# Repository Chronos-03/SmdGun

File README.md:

# Chronos-858D: Custom ESP32-S3 Hot Air Rework Station

## 1. Project Overview
The **Chronos-858D** is a custom-engineered, smart benchtop hot air rework station built around the **ESP32-S3-DevKitC-1** that combines microcontroller precision with robust AC/DC power electronics. Designed from the ground up with a custom 2-layer KiCad PCB and a 3D-printed Fusion 360 enclosure, the station regulates a 220V AC 700W ceramic heating element using  PID control through a  optical isolation stage while independently driving a 24V DC brushless blower fan via PWM. For workshop safety  a physical roller-lever microswitch mounted on the handle cradle automatically detects when the hot air gun is docked, immediately cutting power to the heater coil and running a timed 1-minute cooling cycle until the nozzle drops safely below 50°C, with all real-time temperature measuring, airflow power, and with the stats on a 2.8-inch ILI9341 SPI TFT display controlled by 2 rotary encoders.

---

## 2. Final CAD Renders & Enclosure Design
The enclosure and external handle holder are fully modeled in Fusion 360  for 3D printing in heat-resistant PETG or ABS, and also have an angled front instrument panel and ventilated case that house both the custom main PCB and the 24V 3A industrial SMPS in a compact case. To add tight 3mm thread depths and 3.2mm mounting holes on the display and main circuit board, the internal standoffs are designed around M3 × 3mm knurled brass heat-set inserts paired with M3 × 4mm pan head machine screws, while the side-mounted integrates a recessed slot for a KW11-3Z roller limit switch positioned along the cool lower grip of the 858D handle so the resting weight of the wand actuates the cooldown switch smoothly without exposing the switch body to nozzle heat.

---

## 3. ⚠️ High-Voltage Safety Warning
> **DANGER — 220V–240V AC MAINS VOLTAGE:** This rework station interfaces directly with lethal 220V–240V AC mains electricity to power the 700W heating element and internal SMPS, which presents a severe risk of electrocution, burns, or fire if handled improperly. Always disconnect the main AC power cord from the wall outlet before opening the enclosure, probing the circuit board, or modifying any wiring, and strictly maintain the 2.5mm physical creepage and clearance gap on the PCB between the high-voltage AC heater section and the low-voltage DC microcontroller logic. Ensure that the incoming protective earth ground pin on the IEC320 C14 socket is securely bonded to the metal frame of the 24V SMPS and the insulated-tab BTA16-600B TRIAC heatsink, and insulate all high-voltage solder joints and terminal connections using polyolefin heat shrink tubing and high-temperature polyimide Kapton tape before powering the system.

---

## 4. Electronic Specifications & Pinout
The electrical designing  separates high-voltage AC switching from low-voltage 3.3V digital control across a custom 2-layer  PCB powered by a 24V DC 3A (72W) enclosed SMPS protected by a 2A resettable PTC polyfuse . An onboard LM2596 buck converter  steps the 24V rail down to a regulated 5.0V DC to feed the ESP32-S3-DevKitC-1 , while the 24V blower fan is controllerd through an IRLZ44N logic-level N-channel MOSFET , paired with a 10kΩ gate pull-down resistor , 220Ω gate resistor , and 1N4007 flyback clamping diode . 

On the isolated AC side  protected by a 5A 250V fast-blow glass fuse , HEATER_PWM  drives an MOC3041 zero-crossing optocoupler  through a 150Ω current-limiting resistor , which triggers a 16A 600V BTA16-600B TRIAC  via a 360Ω 1W gate resistor  and a 39Ω 2W / 0.01µF 275VAC X2 RC snubber network . Closed-loop temperature feedback from the handle's K-type thermocouple  is digitized by a MAX6675 cold-junction compensated amplifier  sharing the hardware SPI bus with the non-touch 9-pin 2.8" ILI9341 240×320 TFT display (`J3`), alongside two EC11 rotary encoders  and the holder  limit switch.

## 5. Enclosure & Case Assembly
pressing the M3 × 3mm brass heat-set inserts flush into the 3D-printed mounting bosses inside the front bezel and main chassis floor, then pre-tune the LM2596 buck converter  with a multimeter to output exactly 5.0V DC before seating the ESP32-S3 into its female headers. Next, mount the 2.8-inch ILI9341 TFT display and the populated main PCB onto the internal standoffs using M3 × 4mm pan head screws, fasten the two EC11 rotary encoders and the GX16-8 aviation panel socket to the front face, and bolt the TO-220 aluminum heatsink onto the BTA16-600B TRIAC  with a thin layer of thermal paste. Secure the 24V 3A SMPS to the base of the enclosure double-sided heavy-duty foam tape, snap the IEC320 C14 AC mains inlet switch into the rear panel cutout, and fasten the KW11-3Z roller limit switch onto the external handle cradle using M2 screws and nuts. Finally, wire the 16 AWG silicone power cables from the IEC inlet and SMPS to the screw terminal blocks  and the 24 AWG signal wires from the cradle switch , insulating all exposed AC and DC joints with heat shrink tubing and Kapton tape before closing the case and verifying electrical isolation with a continuity test.

---

## 6. Firmware Architecture & Cooldown Logic
The ESP32-S3 firmware runs a non-blocking C++ control loop that continuously polls the MAX6675 sensor over hardware SPI every 250ms, feeds the nozzle temperature into a PID control algorithm to update the zero-crossing heater duty cycle on `GPIO 4` (`HEATER_PWM`), and refreshes the 2.8-inch ILI9341 TFT display while tracking rotary encoder interrupts for instant target temperature and fan speed adjustments. When the user places the hot air gun into the cradle, the weight of the handle depresses the KW11-3Z roller lever and pulls `GPIO 6` (`REED_SW`) to `GND` (`LOW`), which immediately forces the heater output to `0%`, switches the UI to Cooldown Mode, and locks the 24V blower fan (`GPIO 5`) at 80%–100% speed for a full 1-minute cooldown timer (and until the thermocouple reading drops below 50°C) before shutting the fan off completely and entering low-power

### **Chronos-858D Master Bill of Materials (BOM)**

| # | Component | Supplier | Qty | Total (INR) | Total (USD) | Product Link |
| :--- | :--- | :--- | :---: | :---: | :---: | :--- |
| **1** | Custom 3D-Printed Enclosure + Cradle | PrintLegion | 1 | ₹2,500 | $26.88 | [Link](https://printinglegion.hackclub.com) |
| **2** | Custom 2-Layer PCB Manufacturing | Robu | 1 | ₹900 | $9.68 | [Link](https://robu.in/) |
| **3** | ESP32-S3-DevKitC-1-N8R8 | Robu | 1 | ₹1,839 | $19.77 | [Link](https://robu.in/product/espressif-esp32-s3-devkitc-1-n8r8-development-board/) |
| **4** | 2.4" SPI TFT Touch Screen Module | MakerBazar | 1 | ₹679 | $7.30 | [Link](https://makerbazar.in/products/2-4-inch-spi-interface-240-320-tft-display-module?variant=44937178022128) |
| **5** | MAX6675 Thermocouple Module | MakerBazar | 1 | ₹309 | $3.32 | [Link](https://makerbazar.in/products/max6675-thermocouple-sensor-module) |
| **6** | LM2596 DC-DC Buck Step-Down Module | MakerBazar | 1 | ₹79 | $0.85 | [Link](https://makerbazar.in/products/lm2596-dc-dc-converter-step-down-module?variant=48251191918832) |
| **7** | Quick 858D Replacement Handle (8-wire) | TonyVision | 1 | ₹649 | $6.98 | [Link](https://www.tonyvision.in/product/30533442/Quick-858-Handle-For-858-SMD-Rework-Station--8-Wire-) |
| **8** | GX16-8 Aviation Socket (Panel Mount) | Probots | 1 | ₹160 | $1.72 | [Link](https://probots.co.in/8-pin-gx16-male-to-female-aviation-plug.html) |
| **9** | 24V 3A Metal Enclosed SMPS | ElecComp | 1 | ₹500 | $5.38 | [Link](https://www.electronicscomp.com/24v-3amp-smps-dc-metal-power-supply-nwp-india) |
| **10** | KW11-3Z Roller Lever Micro Switch | MakerBazar | 1 | ₹20 | $0.22 | [Link](https://makerbazar.in/products/automation-direct-limit-switch?variant=46931163742448) |
| **11** | IEC320 C14 AC Mains Socket + Rocker | Probots | 1 | ₹210 | $2.26 | [Link](https://probots.co.in/3-pin-iec320-c14-ac-power-socket-with-fuse-red-rocker-switch-panel-mount-connector.html) |
| **12** | Finned Aluminum Heatsink Kit | MakerBazar | 3 | ₹87 | $0.94 | [Link](https://makerbazar.in/products/3pcs-aluminum-heatsink-with-thermal-tape-for-raspberry-pi-4-model-b-black?variant=48460430213360) |
| **13** | KF301 2-Pin 5.08mm Screw Terminal | Robu | 2 | ₹20 | $0.22 | [Link](https://robu.in/product/kf301-2-pin-5-08mm-pitch-plug-in-screw-terminal-block-connector-pack-of-5/) |
| **14** | 240V AC Power Cord 3-Pin to IEC C-13 | MakerBazar | 1 | ₹159 | $1.71 | [Link](https://makerbazar.in/products/240v-ac-power-cord-3-pin-to-iec-c-13-female-cable?variant=44609024262384) |
| **15** | 20AWG Flexible Silicone Wire (Green) | Robu | 1 | ₹50 | $0.54 | [Link](https://robu.in/product/high-quality-ultra-flexible-20awg-silicone-wire-1000m-green/) |
| **16** | BTA16-600B TRIAC (Pack of 5) | Amazon | 1 | ₹169 | $1.82 | [Link](https://www.amazon.in/pics-BTA16-600B-TRIAC-Volts/dp/B0C9VVTZTV/) |
| **17** | MOC3041M Zero-Cross Optoisolator | Robu | 1 | ₹50 | $0.54 | [Link](https://robu.in/product/moc3041m-ic-zero-cross-optoisolator-triac-driver-ic/) |
| **18** | IRLZ44N Logic-Level N-Channel MOSFET | Robu | 1 | ₹44 | $0.47 | [Link](https://robu.in/product/irlz44n/) |
| **19** | 1N4007 1W Rectifier Diode | Robu | 5 | ₹15 | $0.16 | [Link](https://robu.in/product/1n4007-1w-diode-pack-of-30/) |
| **20** | Hongyan EC11 Rotary Encoders | Robu | 2 | ₹116 | $1.25 | [Link](https://robu.in/product/hongyan-ec11h-7ce20p1zy20-rotary-encoder-with-push-button-switch-vertical-plug-in-5-pin/) |
| **21** | Loose M3 Screws, Nuts & 1m Heat Shrink | Local | 1 | ₹50 | $0.54 | *Local Hardware Store* |
| **22** | 330Ω 1/4W 1206 SMD Resistor | Robu | 1 | ₹15 | $0.16 | [Link](https://robu.in/product/330-ohm-1-4w-1206-surface-mount-chip-resistor-pack-of-100/) |
| **23** | 360Ω 0805 SMD Resistor (Yageo) | Robu | 1 | ₹15 | $0.16 | [Link](https://robu.in/product/rc0805fr-07360rl-yageo-360-ohms-%c2%b11-0-125w-1-8w-chip-resistor-0805-2012-metric-moisture-resistant-thick-film/) |
| **24** | 100Ω 1/4W 1206 SMD Resistor | Robu | 1 | ₹15 | $0.16 | [Link](https://robu.in/product/100-ohm-chip-resistor-1-4w-1206-surface-mount-pack-of-100/) |
| **25** | 10kΩ 0805 SMD Resistor | Amazon | 1 | ₹99 | $1.06 | [Link](https://www.amazon.in/Electronic-Spices-Power-Thick-Resistor/dp/B0BFD96R76/) |
| **26** | 100Ω 2W Carbon Film Resistor | Robu | 1 | ₹2.45 | $0.03 | [Link](https://robu.in/product/100-ohms-2w-carbon-film-resistor-pack-of-50/) |
| **27** | 100nF 400V DIP Polyester Film Cap | Robu | 1 | ₹6.00 | $0.06 | [Link](https://robu.in/product/100nf-400v-dip-polyester-film-capacitor-pitch10mm/) |
| **28** | 100nF 0805 SMD Ceramic Capacitor | Robu | 3 | ₹2.37 | $0.03 | [Link](https://robu.in/product/100nf-0805-surface-mount-multilayer-ceramic-capacitor-pack-of-40/) |
| **29** | 100µF 35V SMD Tantalum Capacitor | Robu | 1 | ₹57.00 | $0.61 | [Link](https://robu.in/product/100uf-35v-10-d-case-chip-tantalum-capacitorsmd-avx/) |
| **30** | DHRUV-PRO 120x120x38mm 24V Cooling Fan | Amazon | 1 | ₹579.00 | $6.23 | [Link](https://www.amazon.in/DHRUV-PRO-120X120X38mm-Cooling-120x120x38-MM-2800-RPM/dp/B0BTMC17SK/) |
| | **FINAL GRAND TOTAL** | | | **₹9,395.82** | **$101.05** | |

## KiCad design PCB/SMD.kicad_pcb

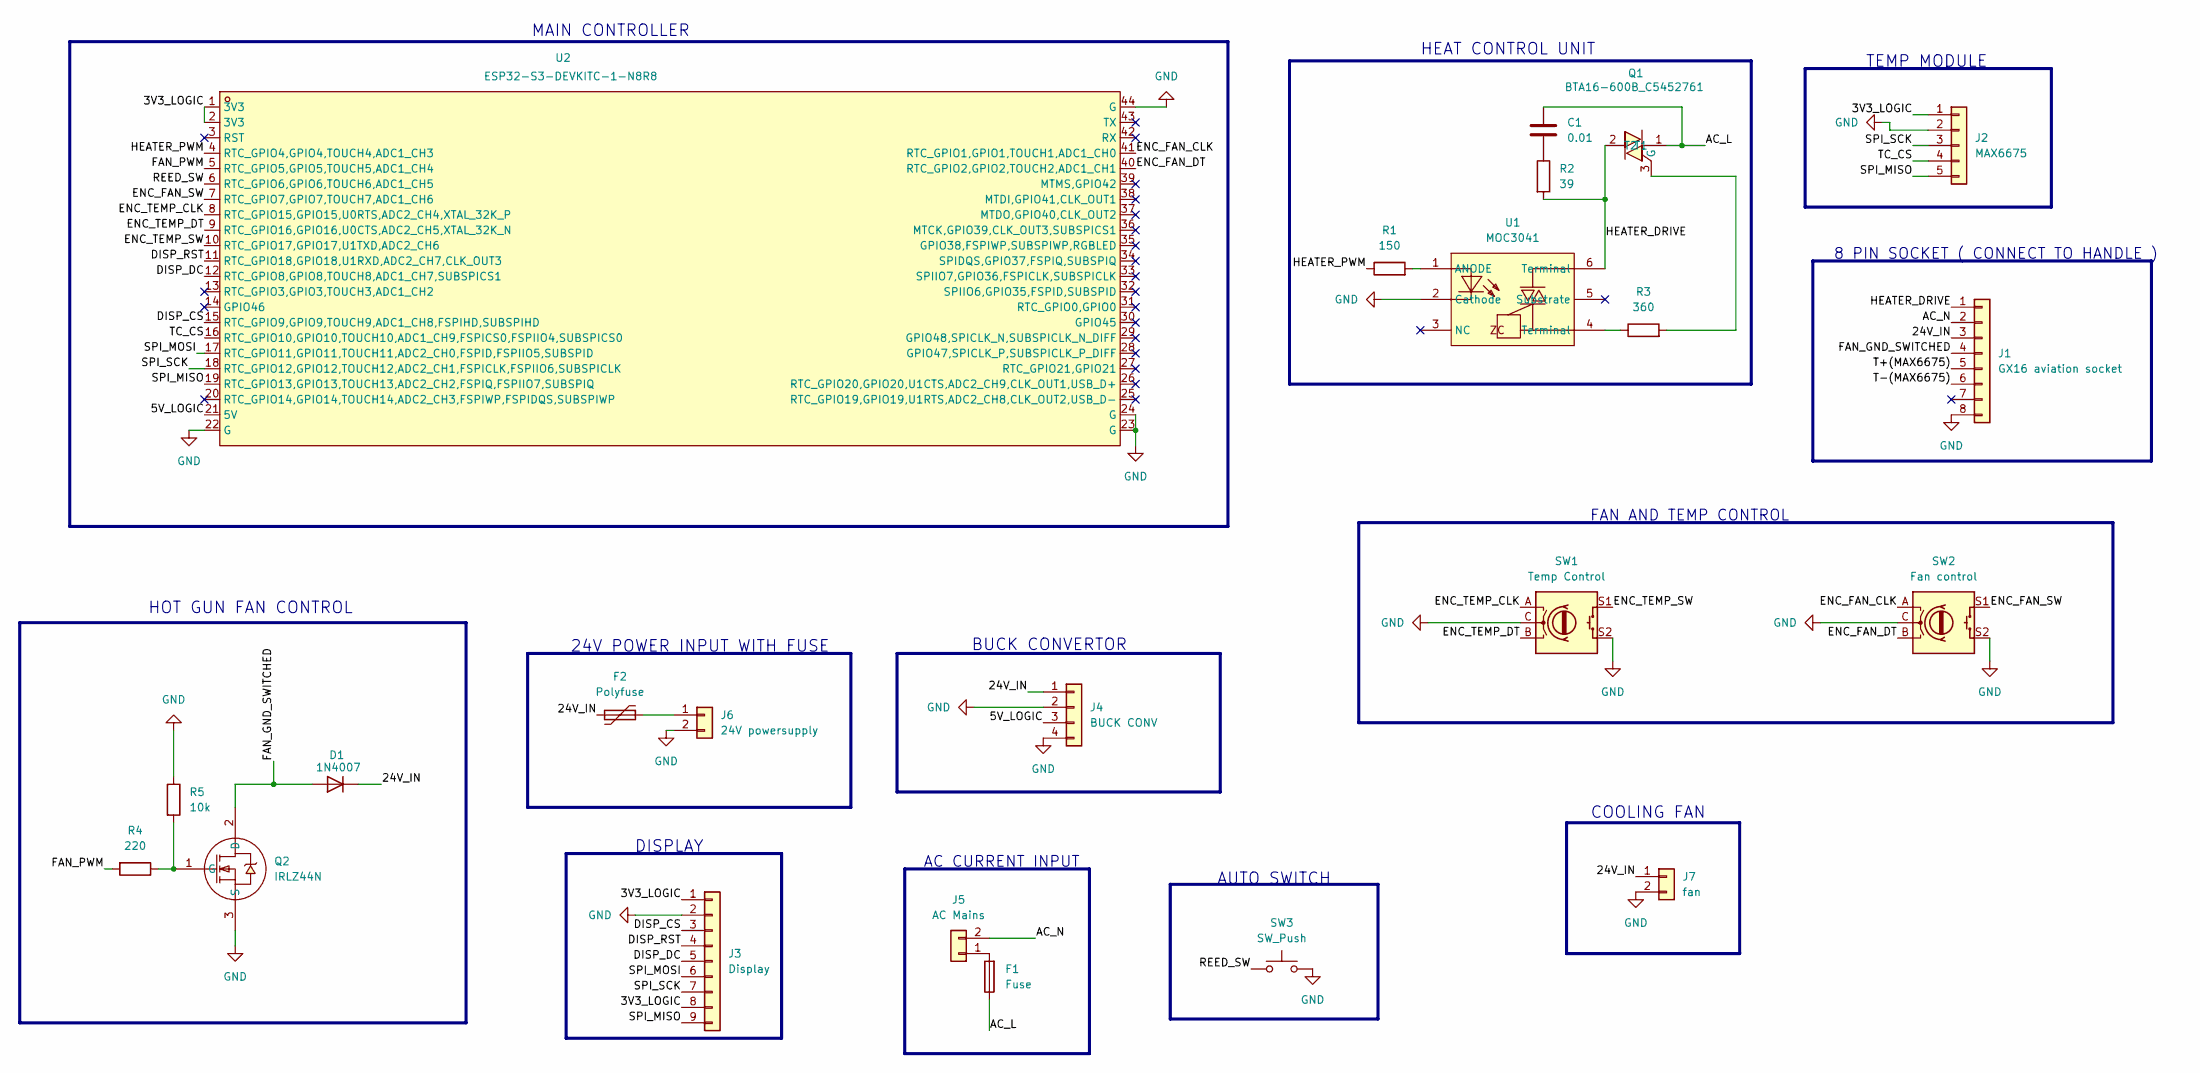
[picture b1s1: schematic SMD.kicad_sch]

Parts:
C1: 0.01; C_Rect_L18.0mm_W5.0mm_P15.00mm_FKS3_FKP3
D1: 1N4007; D_DO-41_SOD81_P10.16mm_Horizontal
F1: Fuse; Fuseholder_Cylinder-5x20mm_Schurter_0031_8201_Horizontal_Op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
F2: Polyfuse; Fuse_Bourns_MF-RHT200
J1: GX16 aviation socket; PinHeader_1x08_P2.54mm_Horizontal
J2: MAX6675; PinHeader_1x05_P2.54mm_Horizontal
J3: Display; PinHeader_1x09_P2.54mm_Horizontal
J4: BUCK CONV; PinHeader_1x04_P2.54mm_Horizontal
J5: AC Mains; TerminalBlock_Phoenix_MKDS-1,5-2-5.08_1x02_P5.08mm_Horizont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
J6: 24V powersupply; TerminalBlock_Phoenix_MKDS-1,5-2-5.08_1x02_P5.08mm_Horizont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
J7: fan; PinHeader_1x02_P2.54mm_Vertical
Q1: BTA16-600B_C5452761; TO-220-3_L10.0-W4.5-P2.54-L_1; MPN BTA16-600B; LCSC Part C5452761
Q2: IRLZ44N; TO-220-3_L10.2-W4.5-P2.54-L; MPN IRLZ44N(UMW); LCSC Part C42370423
R1: 150; R_0805_2012Metric
R2: 39; R_Axial_DIN0414_L11.9mm_D4.5mm_P15.24mm_Horizontal
R3: 360; R_0805_2012Metric
R4: 220; R_0805_2012Metric
R5: 10k; R_0805_2012Metric
SW1: Temp Control; RotaryEncoder_Alps_EC11E-Switch_Vertical_H20mm
SW2: Fan control; RotaryEncoder_Alps_EC11E-Switch_Vertical_H20mm
SW3: SW_Push; PinHeader_1x02_P2.54mm_Vertical
U1: MOC3041; DIP-6_L7.3-W6.5-P2.54-LS7.6-BL; MPN MOC3041; LCSC Part C6177963
U2: ESP32-S3-DEVKITC-1-N8R8; CONN-TH_ESP32-S3-DEVKITC-1U-N8; MPN ESP32-S3-DEVKITC-1-N8R8; LCSC Part C20541519

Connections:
/3V3_LOGIC: J2.1, J3.1, J3.8, U2.1 (3V3), U2.2 (3V3)
/5V_LOGIC: J4.3, U2.21 (5V)
/24V_IN: D1.1 (K), F2.2, J1.3, J4.1, J7.1
/AC_L: C1.1, F1.1, Q1.1 (T1)
/AC_N: J1.2, J5.2
/DISP_CS: J3.3, U2.15 (RTC_GPIO9,GPIO9,TOUCH9,ADC1_CH8,FSPIHD,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)
/DISP_DC: J3.5, U2.12 (RTC_GPIO8,GPIO8,TOUCH8,ADC1_CH7,SUBSPIC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)
/DISP_RST: J3.4, U2.11 (RTC_GPIO18,GPIO18,U1RXD,ADC2_CH7,CLK_OU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)
/ENC_FAN_CLK: SW2.A, U2.41 (RTC_GPIO1,GPIO1,TOUCH1,ADC1_CH0)
/ENC_FAN_DT: SW2.B, U2.40 (RTC_GPIO2,GPIO2,TOUCH2,ADC1_CH1)
/ENC_FAN_SW: SW2.S1, U2.7 (RTC_GPIO7,GPIO7,TOUCH7,ADC1_CH6)
/ENC_TEMP_CLK: SW1.A, U2.8 (RTC_GPIO15,GPIO15,U0RTS,ADC2_CH4,XTAL_3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)
/ENC_TEMP_DT: SW1.B, U2.9 (RTC_GPIO16,GPIO16,U0CTS,ADC2_CH5,XTAL_3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)
/ENC_TEMP_SW: SW1.S1, U2.10 (RTC_GPIO17,GPIO17,U1TXD,ADC2_CH6)
/FAN_GND_SWITCHED: D1.2 (A), J1.4, Q2.2 (D)
/FAN_PWM: R4.2, U2.5 (RTC_GPIO5,GPIO5,TOUCH5,ADC1_CH4)
/HEATER_DRIVE: J1.1, Q1.2 (T2), R2.2, U1.6 (Terminal)
/HEATER_PWM: R1.1, U2.4 (RTC_GPIO4,GPIO4,TOUCH4,ADC1_CH3)
/REED_SW: SW3.1, U2.6 (RTC_GPIO6,GPIO6,TOUCH6,ADC1_CH5)
/SPI_MISO: J2.5, J3.9, U2.19 (RTC_GPIO13,GPIO13,TOUCH13,ADC2_CH2,FSPI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)
/SPI_MOSI: J3.6, U2.17 (RTC_GPIO11,GPIO11,TOUCH11,ADC2_CH0,FSPI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)
/SPI_SCK: J2.3, J3.7, U2.18 (RTC_GPIO12,GPIO12,TOUCH12,ADC2_CH1,FSPI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)
/T+(MAX6675): J1.5
/T-(MAX6675): J1.6
/TC_CS: J2.4, U2.16 (RTC_GPIO10,GPIO10,TOUCH10,ADC1_CH9,FSPI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)
GND: J1.8, J2.2, J3.2, J4.2, J4.4, J6.2, J7.2, Q2.3 (S), R5.1, SW1.C, SW1.S2, SW2.C, SW2.S2, SW3.2, U1.2 (Cathode), U2.22 (G), U2.23 (G), U2.24 (G), U2.44 (G)
unnamed: C1.2, R2.1
unnamed: F1.2, J5.1
unnamed: F2.1, J6.1
unnamed: Q1.3 (G), R3.2
unnamed: Q2.1 (G), R4.1, R5.2
unnamed: R3.1, U1.4 (Terminal)
unnamed: R1.2, U1.1 (ANODE)

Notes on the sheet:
HOT GUN FAN CONTROL
DISPLAY
MAIN CONTROLLER
AUTO SWITCH
BUCK CONVERTOR
AC CURRENT INPUT
TEMP MODULE
24V POWER INPUT WITH FUSE
8 PIN SOCKET ( CONNECT TO HANDLE )
FAN AND TEMP CONTROL
HEAT CONTROL UNIT
COOLING FAN

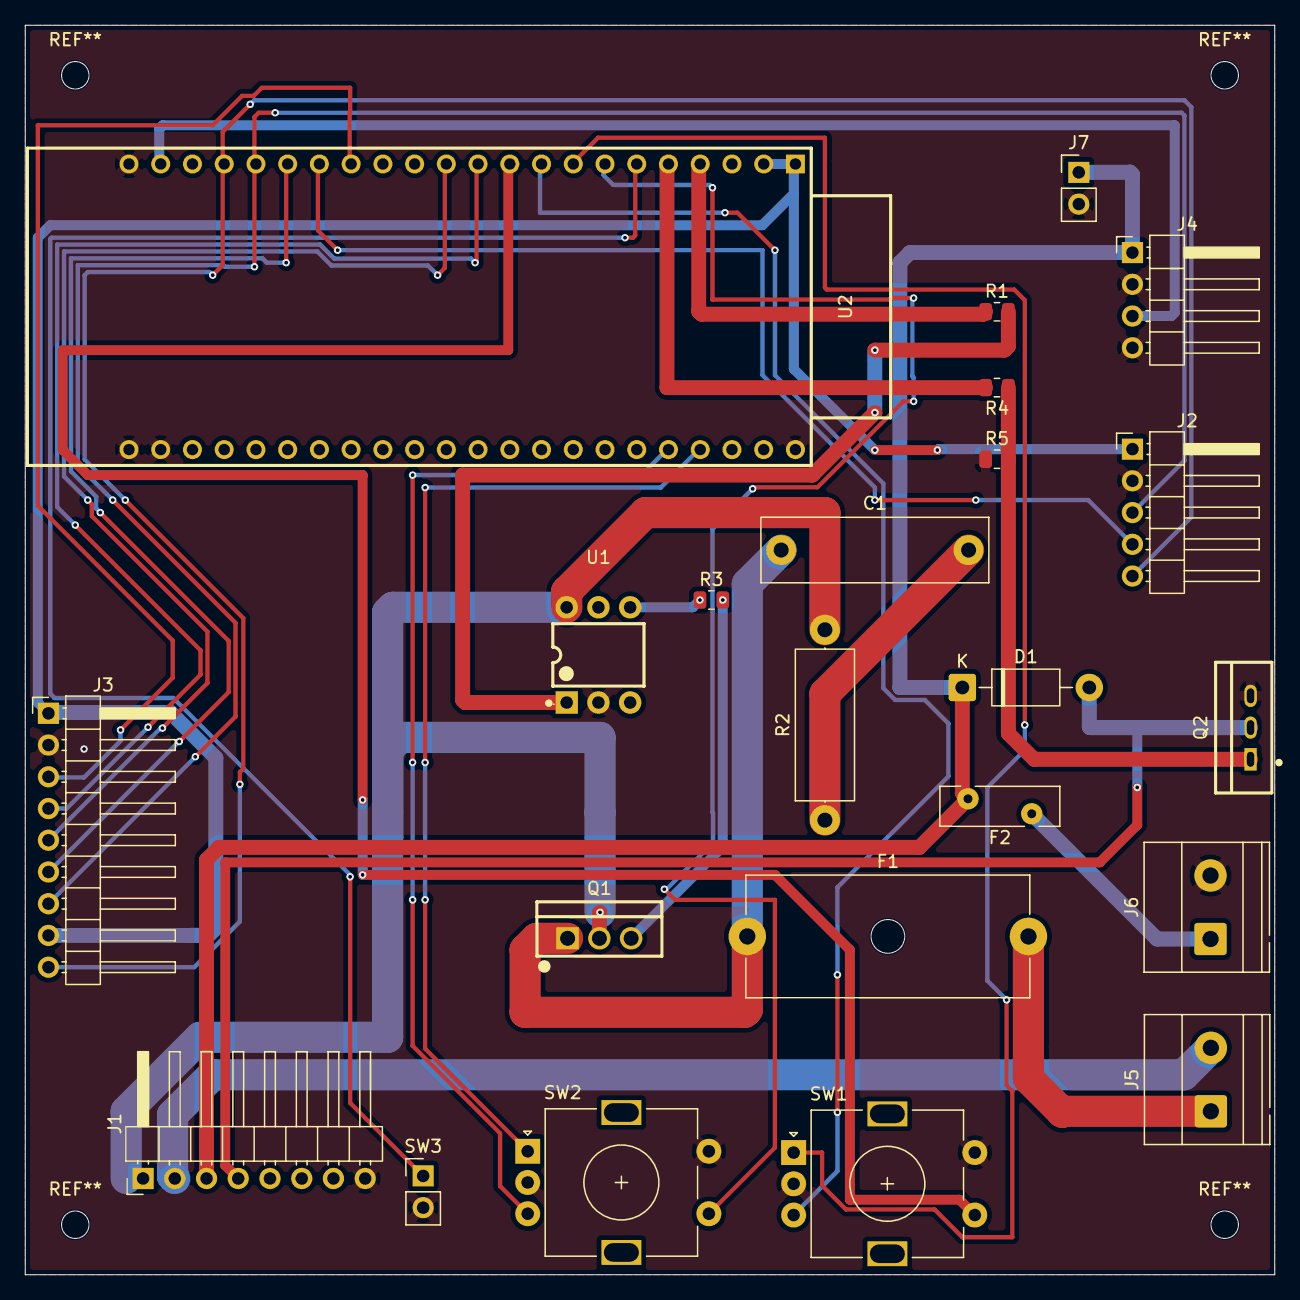
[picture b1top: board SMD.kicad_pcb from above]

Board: 2 copper layers, 100.0 x 100.0 mm, 23 parts (0 on the bottom side), 31 nets.

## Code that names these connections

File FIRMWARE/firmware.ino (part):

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#include <Adafruit_GFX.h>
#include <Adafruit_ILI9341.h>

#define PIN_HEATER_PWM    4
#define PIN_FAN_PWM       5
#define PIN_REED_SW       6

#define PIN_DISP_DC       8
#define PIN_DISP_CS       9
#define PIN_TC_CS         10
#define PIN_SPI_MOSI      11
#define PIN_SPI_SCK       12
#define PIN_SPI_MISO      13
#define PIN_DISP_RST      18

#define PIN_ENC1_A        33
#define PIN_ENC1_B        34
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volatile unsigned long enc1LastUs = 0;
volatile unsigned long enc2LastUs = 0;

Adafruit_ILI9341 tft = Adafruit_ILI9341(&SPI, PIN_DISP_DC, PIN_DISP_CS, PIN_DISP_RST);

#define FAN_PWM_FREQ_HZ  25000
#define FAN_PWM_RES_BITS 8

void initFanPWM() {
#if ESP_ARDUINO_VERSION >= ESP_ARDUINO_VERSION_VAL(3, 0, 0)
  ledcAttach(PIN_FAN_PWM, FAN_PWM_FREQ_HZ, FAN_PWM_RES_BITS);
#else
  ledcSetup(0, FAN_PWM_FREQ_HZ, FAN_PWM_RES_BITS);
  ledcAttachPin(PIN_FAN_PWM, 0);
#endif
}

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  pct = constrain(pct, 0, 100);
  uint32_t duty = (pct == 0) ? 0 : map(pct, 1, 100, 55, 255);
#if ESP_ARDUINO_VERSION >= ESP_ARDUINO_VERSION_VAL(3, 0, 0)
  ledcWrite(PIN_FAN_PWM, duty);
#else
  ledcWrite(0, duty);
#endif
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}

float readMAX6675HardwareSPI(bool &faultOut) {
  digitalWrite(PIN_DISP_CS, HIGH);
  SPI.beginTransaction(SPISettings(4000000, MSBFIRST, SPI_MODE0));
  digitalWrite(PIN_TC_CS, LOW);
  delayMicroseconds(2);
  uint16_t raw = SPI.transfer16(0x0000);
  digitalWrite(PIN_TC_CS, HIGH);
  SPI.endTransaction();

  if (raw & 0x0004) {
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
void runHeaterZeroCrossWindow() {
  if (currentState != STATE_ACTIVE_HEATING || sensorFault) {
    digitalWrite(PIN_HEATER_PWM, LOW);
    heaterDutyWindowMs = 0.0f;
    return;
  }
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  }

  if ((now - windowStartTime) < (unsigned long)heaterDutyWindowMs) {
    digitalWrite(PIN_HEATER_PWM, HIGH);
  } else {
    digitalWrite(PIN_HEATER_PWM, LOW);
  }
}

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void setup() {
  Serial.begin(115200);

  pinMode(PIN_HEATER_PWM, OUTPUT);
  digitalWrite(PIN_HEATER_PWM, LOW);

  pinMode(PIN_REED_SW, INPUT_PULLUP);

  initFanPWM();
  setFanSpeedPercent(0);
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  attachInterrupt(digitalPinToInterrupt(PIN_ENC1_A), isrEncoderTemp, CHANGE);
  attachInterrupt(digitalPinToInterrupt(PIN_ENC2_A), isrEncoderFan, CHANGE);

  pinMode(PIN_TC_CS, OUTPUT);
  digitalWrite(PIN_TC_CS, HIGH);
  pinMode(PIN_DISP_CS, OUTPUT);
  digitalWrite(PIN_DISP_CS, HIGH);

  SPI.begin(PIN_SPI_SCK, PIN_SPI_MISO, PIN_SPI_MOSI);

  tft.begin();
  tft.setRotation(1);
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    if (sensorFault || actualTempC >= TEMP_OVERHEAT_LIMIT_C) {
      sensorFault = true;
      currentState = STATE_SENSOR_FAULT;
      digitalWrite(PIN_HEATER_PWM, LOW);
      setFanSpeedPercent(100);
    } else {
      bool gunOnCradle = (digitalRead(PIN_REED_SW) == LOW);

      if (gunOnCradle) {
        digitalWrite(PIN_HEATER_PWM, LOW);
        heaterDutyWindowMs = 0.0f;
        pidIntegral = 0.0f;

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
